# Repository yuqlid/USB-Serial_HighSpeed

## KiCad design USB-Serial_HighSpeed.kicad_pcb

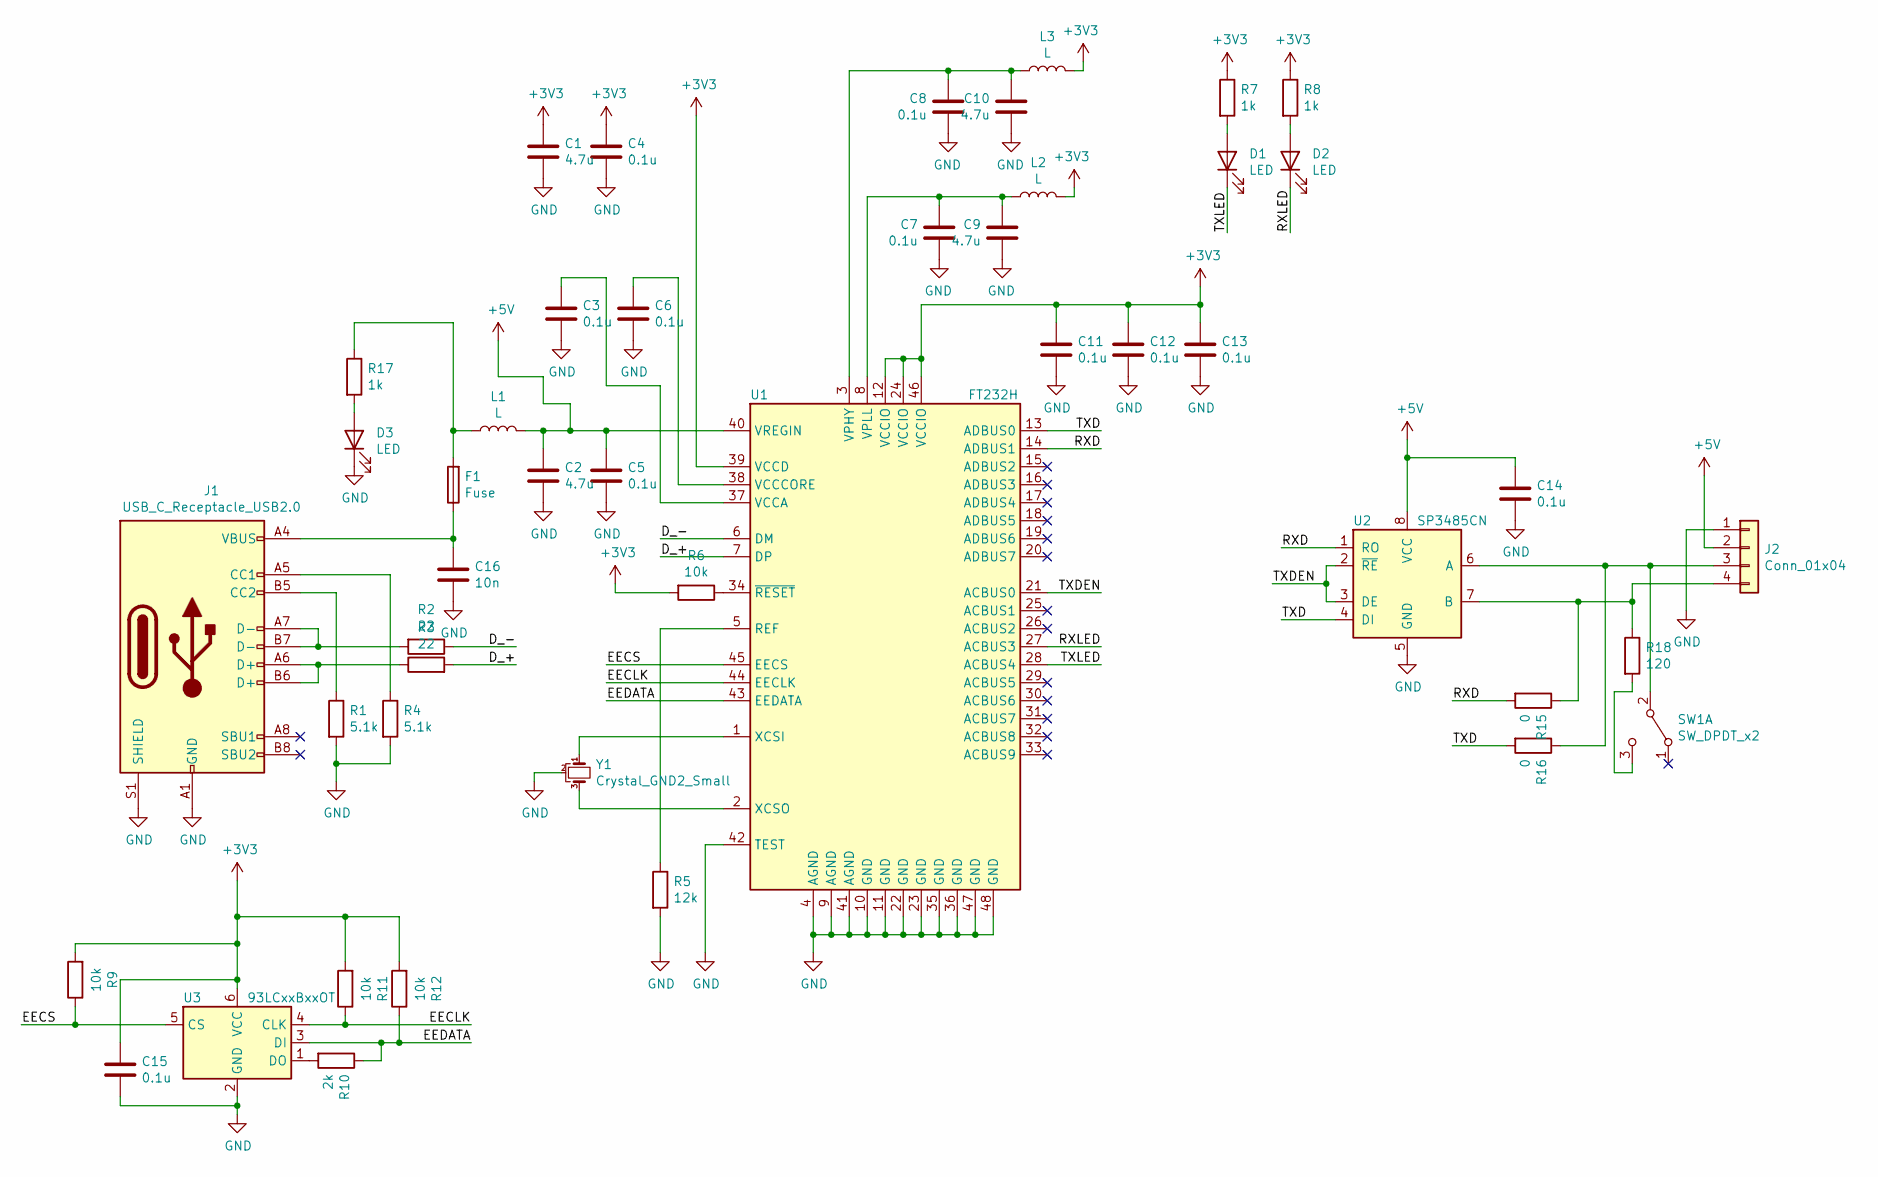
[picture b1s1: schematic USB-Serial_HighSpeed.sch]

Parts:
C1, C2, C9, C10: 4.7u; C_0603_1608Metric
C3, C4, C5, C6, C7, C8, C11, C12, C13, C14, C15: 0.1u; C_0402_1005Metric
C16: 10n; C_0402_1005Metric
D1, D2, D3: LED; LED_0603_1608Metric
F1: Fuse; Fuse_0603_1608Metric
J1: USB_C_Receptacle_USB2.0; USB_C_Receptacle_GCT_USB4085
J2: Conn_01x04; PinHeader_1x04_P2.54mm_Horizontal
L1, L2, L3: L; L_0603_1608Metric
R1, R4: 5.1k; R_0402_1005Metric
R2, R3: 22; R_0402_1005Metric
R5: 12k; R_0402_1005Metric
R6, R9, R11, R12: 10k; R_0402_1005Metric
R7, R8, R17: 1k; R_0402_1005Metric
R10: 2k; R_0402_1005Metric
R15, R16: 0; R_0402_1005Metric
R18: 120; R_0603_1608Metric
SW1: SW_DPDT_x2; SW_SPDT_PCM12
U1: FT232H; LQFP-48_7x7mm_P0.5mm
U2: SP3485CN; SOIC-8_3.9x4.9mm_P1.27mm
U3: 93LCxxBxxOT; SOT-23-6
Y1: Crystal_GND2_Small; Resonator_SMD_muRata_CSTxExxV-3Pin_3.0x1.1mm

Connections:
+3V3: C1.1, C4.1, C11.1, C12.1, C13.1, C15.1, L2.1, L3.1, R6.2, R7.1, R8.1, R9.2, R11.2, R12.2, U1.12 (VCCIO), U1.24 (VCCIO), U1.39 (VCCD), U1.46 (VCCIO), U3.6 (VCC)
+5V: C2.1, C5.1, C14.1, J2.2, L1.2, U1.40 (VREGIN), U2.8 (VCC)
/D_+: R3.2, U1.7 (DP)
/D_-: R2.1, U1.6 (DM)
/EECLK: R11.1, U1.44 (EECLK), U3.4 (CLK)
/EECS: R9.1, U1.45 (EECS), U3.5 (CS)
/EEDATA: R10.1, R12.1, U1.43 (EEDATA), U3.3 (DI)
/RXD: R15.2, U1.14 (ADBUS1), U2.1 (RO)
/RXLED: D2.1 (K), U1.27 (ACBUS3)
/TXD: R16.2, U1.13 (ADBUS0), U2.4 (DI)
/TXDEN: U1.21 (ACBUS0), U2.2 (~RE~), U2.3 (DE)
/TXLED: D1.1 (K), U1.28 (ACBUS4)
GND: C1.2, C2.2, C3.2, C4.2, C5.2, C6.2, C7.2, C8.2, C9.2, C10.2, C11.2, C12.2, C13.2, C14.2, C15.2, C16.2, D3.1 (K), J1.A1 (GND), J1.A12 (GND), J1.B1 (GND), J1.B12 (GND), J1.S1 (SHIELD), J2.1, R1.2, R4.2, R5.2, U1.4 (AGND), U1.9 (AGND), U1.10 (GND), U1.11 (GND), U1.22 (GND), U1.23 (GND), U1.35 (GND), U1.36 (GND), U1.41 (AGND), U1.42 (TEST), U1.47 (GND), U1.48 (GND), U2.5 (GND), U3.2 (GND), Y1.2
unnamed: C3.1, U1.37 (VCCA)
unnamed: C6.1, U1.38 (VCCCORE)
unnamed: C7.1, C9.1, L2.2, U1.8 (VPLL)
unnamed: C8.1, C10.1, L3.2, U1.3 (VPHY)
unnamed: C16.1, F1.1, J1.A4 (VBUS), J1.A9 (VBUS), J1.B4 (VBUS), J1.B9 (VBUS)
unnamed: D1.2 (A), R7.2
unnamed: D2.2 (A), R8.2
unnamed: D3.2 (A), R17.2
unnamed: F1.2, L1.1, R17.1
unnamed: J1.A5 (CC1), R4.1
unnamed: J1.A6 (D+), J1.B6 (D+), R3.1
unnamed: J1.A7 (D-), J1.B7 (D-), R2.2
unnamed: J1.B5 (CC2), R1.1
unnamed: J2.3, R16.1, SW1.2 (B), U2.6 (A)
unnamed: J2.4, R15.1, R18.1, U2.7 (B)
unnamed: R5.1, U1.5 (REF)
unnamed: R6.1, U1.34 (~RESET)
unnamed: R10.2, U3.1 (DO)
unnamed: R18.2, SW1.3 (C)
unnamed: U1.1 (XCSI), Y1.1
unnamed: U1.2 (XCSO), Y1.3

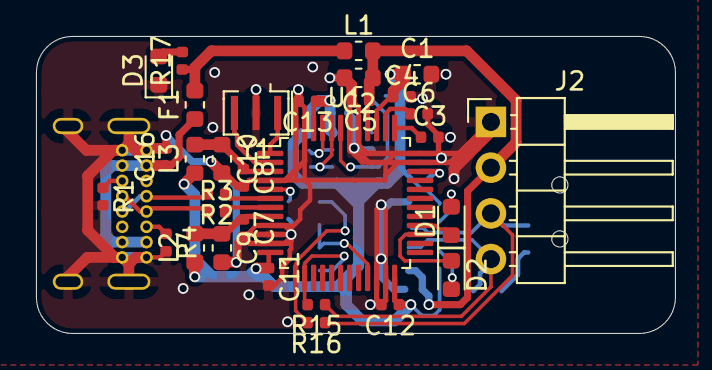
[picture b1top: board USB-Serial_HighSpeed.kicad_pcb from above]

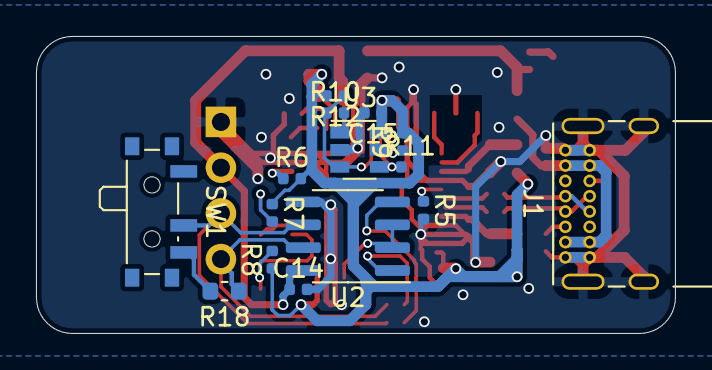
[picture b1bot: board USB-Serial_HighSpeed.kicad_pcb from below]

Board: 2 copper layers, 35.5 x 16.5 mm, 46 parts (15 on the bottom side), 34 nets.

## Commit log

2020-08-17 GND調整
2020-08-19 これで出す
2020-08-27 Create LICENSE
